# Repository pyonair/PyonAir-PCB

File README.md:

# PyonAir-PCB

This repository contains the files for the PyonAir air pollution monitor PCB.
These include:
-Eagle .brd and .sch files, which can be used to redesign the PCB.
-Zipped Gerber files, which are sent to PCB manufacturers.
-BOM for PCBA services

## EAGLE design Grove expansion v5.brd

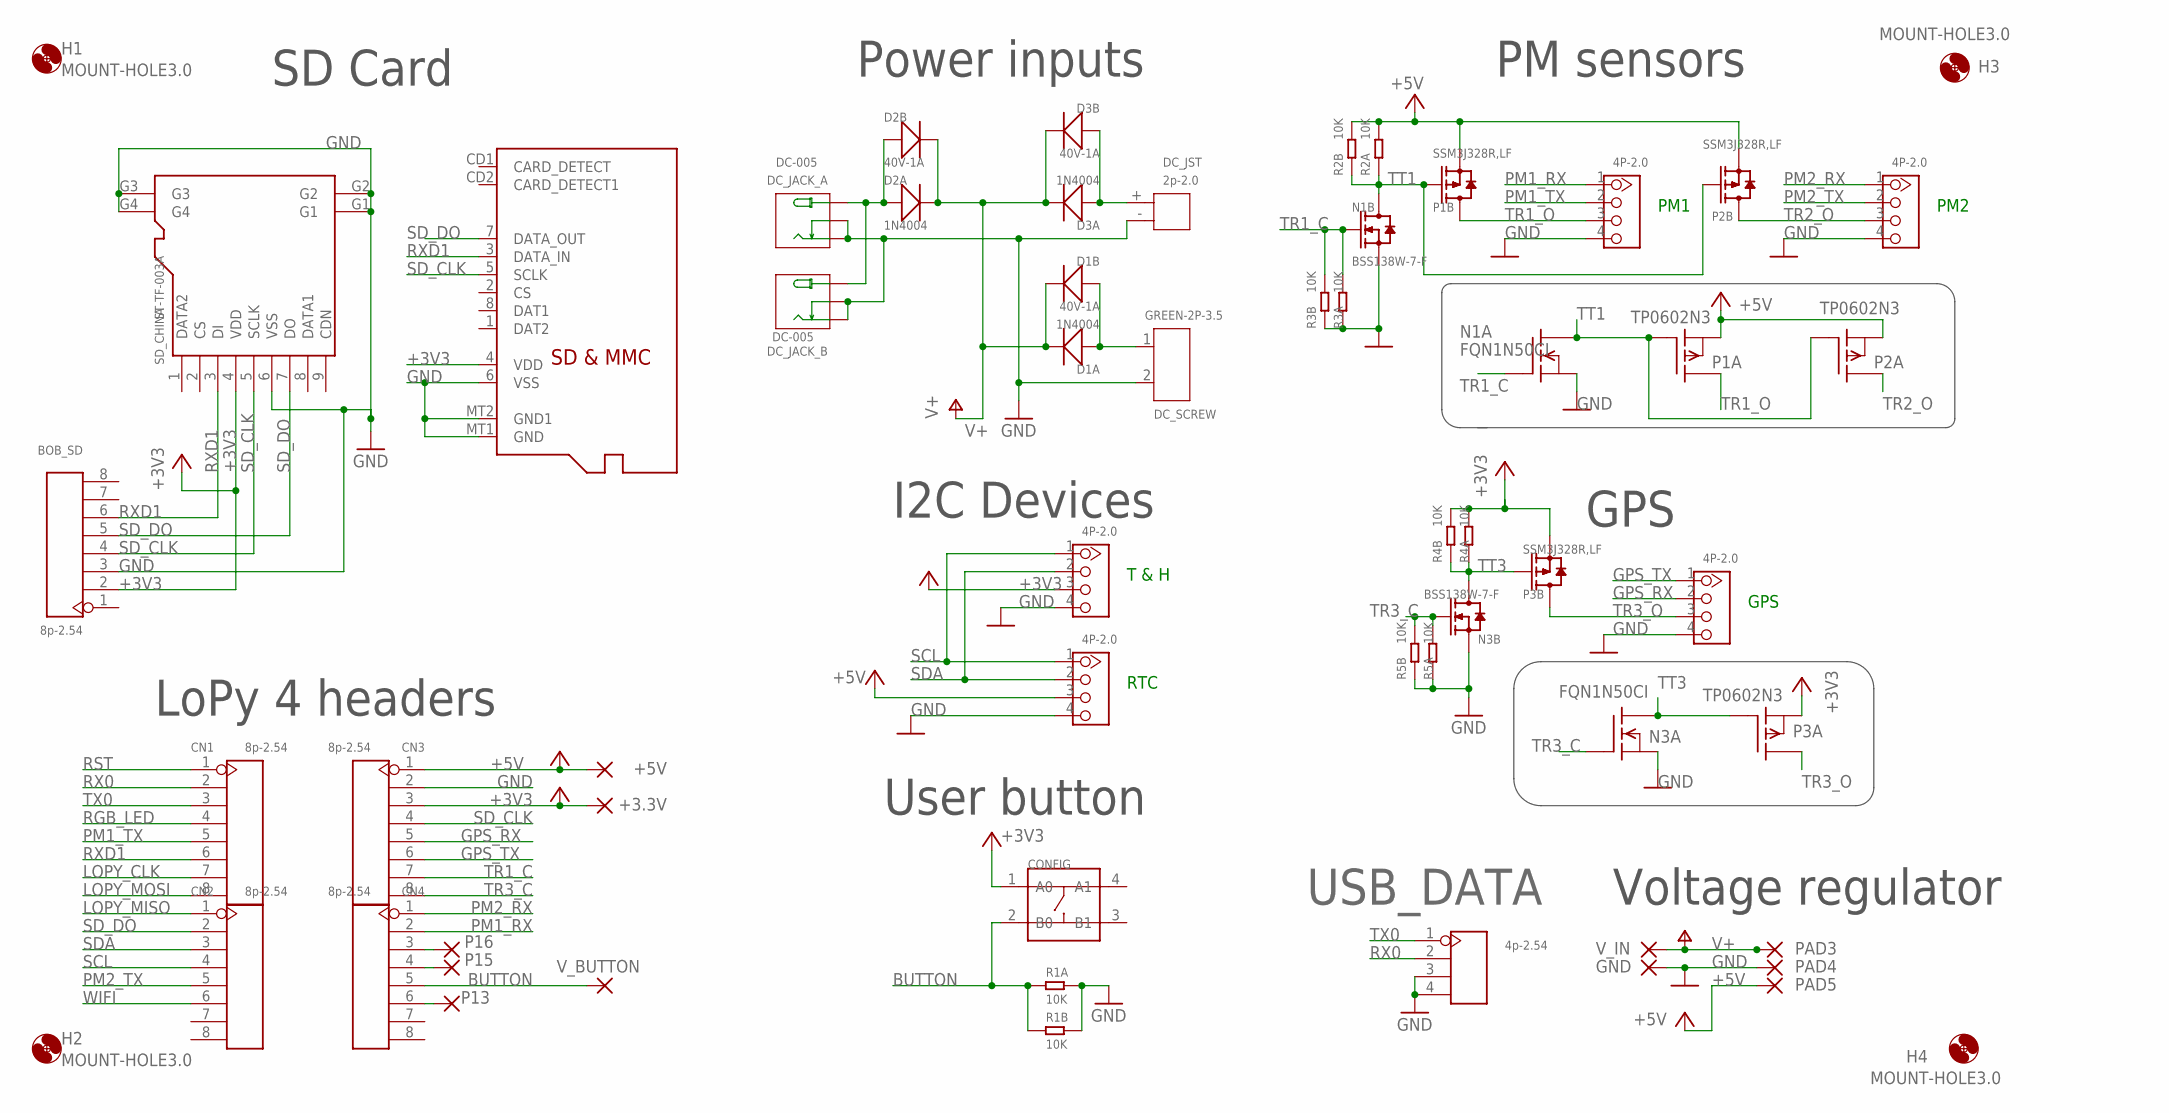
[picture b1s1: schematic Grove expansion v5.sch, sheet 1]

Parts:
+3.3V: 3.3V; 2,15/1,0
+5V: 5V; 2,15/1,0
BOB_SD: 8p-2.54; H8-2.54
CN1, CN2, CN3, CN4: 8p-2.54; H8-2.54
CONFIG: DIP-SWITCH-TACTILE-SPST-NO/TS-1109(4P-D6.0MM)'TS-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; SW4-6.0X6.0X5.0MM
D1A, D2A, D3A: 1N4004; DO-41
D1B, D2B, D3B: 40V-1A; DO-214AC
DC_JACK_A: DC-005; DCJ3P-14.2X11.0X9.0MM
DC_JACK_B: DC-005; DCJ3P-14.2X11.0X9.0MM
DC_JST: 2p-2.0; H2-2.0-6X4.5MM
DC_SCREW: GREEN-2P-3.5; H2-3.5-7.0X7.0MM
GND: 0V; 2,15/1,0
GPS-(DIG): 4P-2.0; HW4-2.0
H1, H2, H3, H4: MOUNT-HOLE3.0; 3,0
N1A, N3A: FQN1N50CI; TO92-INLINE
N1B, N3B: BSS138W-7-F; SOT-23
P1A, P2A, P3A: TP0602N3; TO-92
P1B, P2B, P3B: SSM3J328R,LF; SOT-23
P13, P15, P16: 2,15/1,0
PAD3: 12V; 1,6/0,8
PAD4: 0V; 1,6/0,8
PAD5: 5V; 1,6/0,8
PM1-(UART), PM2-(UART): 4P-2.0; HW4-2.0
R1A, R2A, R3A, R4A, R5A: 10K; PR-D2.3XL6.5MM
R1B, R2B, R3B, R4B, R5B: 10K; R0603
RTC-(I2C): 4P-2.0; HW4-2.0
SD_CHINA: ST-TF-003A; MICRO-SD9+4P-SMD-16.1X14.5X1.85MM
SD_UK: MICROSD
TH-(I2C): 4P-2.0; HW4-2.0
USB_DATA: 4p-2.54; H4-2.54
V_BUTTON: 3.3V; 2,15/1,0
V_IN: 12V; 2,15/1,0

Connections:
+3V3: +3.3V.1, BOB_SD.2, CN3.3, CONFIG.1 (A0), P3A.1 (S), P3B.2 (S), R4A.2, R4B.2, SD_CHINA.4 (VDD), SD_UK.4 (VDD), TH-(I2C).3
+5V: +5V.1, CN3.1, P1A.1 (S), P1B.2 (S), P2A.1 (S), P2B.2 (S), PAD5.1, R2A.2, R2B.2, RTC-(I2C).3
BUTTON: CN4.5, CONFIG.2 (B0), R1A.1, R1B.1, V_BUTTON.1
GND: BOB_SD.3, CN3.2, DC_JACK_A.-1 (-), DC_JACK_A.-2 (CDN), DC_JACK_B.-1 (-), DC_JACK_B.-2 (CDN), DC_JST.-, DC_SCREW.2, GND.1, GPS-(DIG).4, N1A.3 (S), N1B.2 (S), N3A.3 (S), N3B.2 (S), PAD4.1, PM1-(UART).4, PM2-(UART).4, R1A.2, R1B.2, R3A.1, R3B.1, R5A.1, R5B.1, RTC-(I2C).4, SD_CHINA.6 (VSS), SD_CHINA.G1, SD_CHINA.G2, SD_CHINA.G3, SD_CHINA.G4, SD_UK.6 (VSS), SD_UK.MT1 (GND), SD_UK.MT2 (GND1), TH-(I2C).4, USB_DATA.3, USB_DATA.4
GPS_RX: CN3.5, GPS-(DIG).2
GPS_TX: CN3.6, GPS-(DIG).1
JACK_V+: D2A.1 (+), D2B.1 (+), DC_JACK_A.+, DC_JACK_B.+
JST_V+: D3A.1 (+), D3B.1 (+), DC_JST.+
LOPY_CLK: CN1.7
LOPY_MISO: CN2.1
LOPY_MOSI: CN1.8
P13: CN4.6, P13.1
P15: CN4.4, P15.1
P16: CN4.3, P16.1
PM1_RX: CN4.2, PM1-(UART).1
PM1_TX: CN1.5, PM1-(UART).2
PM2_RX: CN4.1, PM2-(UART).1
PM2_TX: CN2.5, PM2-(UART).2
RGB_LED: CN1.4
RST: CN1.1
RX0: CN1.2, USB_DATA.2
RXD1: BOB_SD.6, CN1.6, SD_CHINA.3 (DI), SD_UK.3 (DATA_IN)
SCL: CN2.4, RTC-(I2C).1, TH-(I2C).1
SCREW_V+: D1A.1 (+), D1B.1 (+), DC_SCREW.1
SDA: CN2.3, RTC-(I2C).2, TH-(I2C).2
SD_CLK: BOB_SD.4, CN3.4, SD_CHINA.5 (SCLK), SD_UK.5 (SCLK)
SD_DO: BOB_SD.5, CN2.2, SD_CHINA.7 (DO), SD_UK.7 (DATA_OUT)
TR1_C: CN3.7, N1A.2 (G), N1B.1 (G), R3A.2, R3B.2
TR1_O: P1A.3 (D), P1B.3 (D), PM1-(UART).3
TR2_O: P2A.3 (D), P2B.3 (D), PM2-(UART).3
TR3_C: CN3.8, N3A.2 (G), N3B.1 (G), R5A.2, R5B.2
TR3_O: GPS-(DIG).3, P3A.3 (D), P3B.3 (D)
TT1: N1A.1 (D), N1B.3 (D), P1A.2 (G), P1B.1 (G), P2A.2 (G), P2B.1 (G), R2A.1, R2B.1
TT3: N3A.1 (D), N3B.3 (D), P3A.2 (G), P3B.1 (G), R4A.1, R4B.1
TX0: CN1.3, USB_DATA.1
V+: D1A.2 (-), D1B.2 (-), D2A.2 (-), D2B.2 (-), D3A.2 (-), D3B.2 (-), PAD3.1, V_IN.1
WIFI: CN2.6

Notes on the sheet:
PM1
PM2
T & H
GPS
RTC
Power inputs
User button
Voltage regulator
PM sensors
SD Card
LoPy 4 headers
I2C Devices

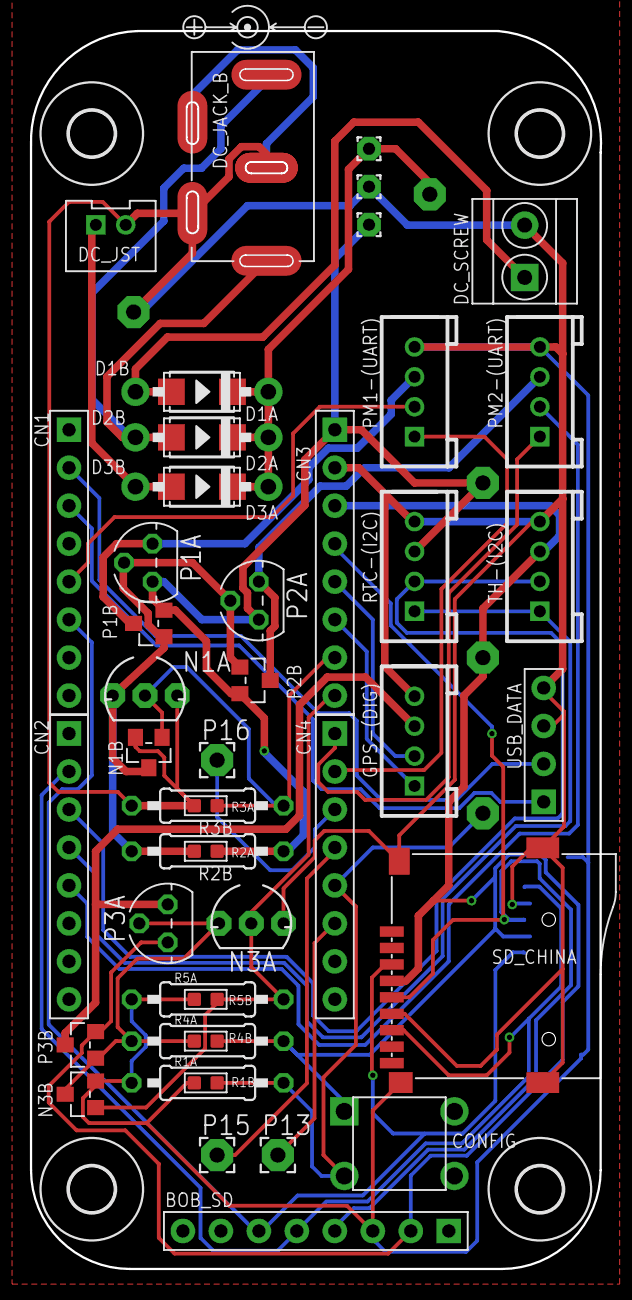
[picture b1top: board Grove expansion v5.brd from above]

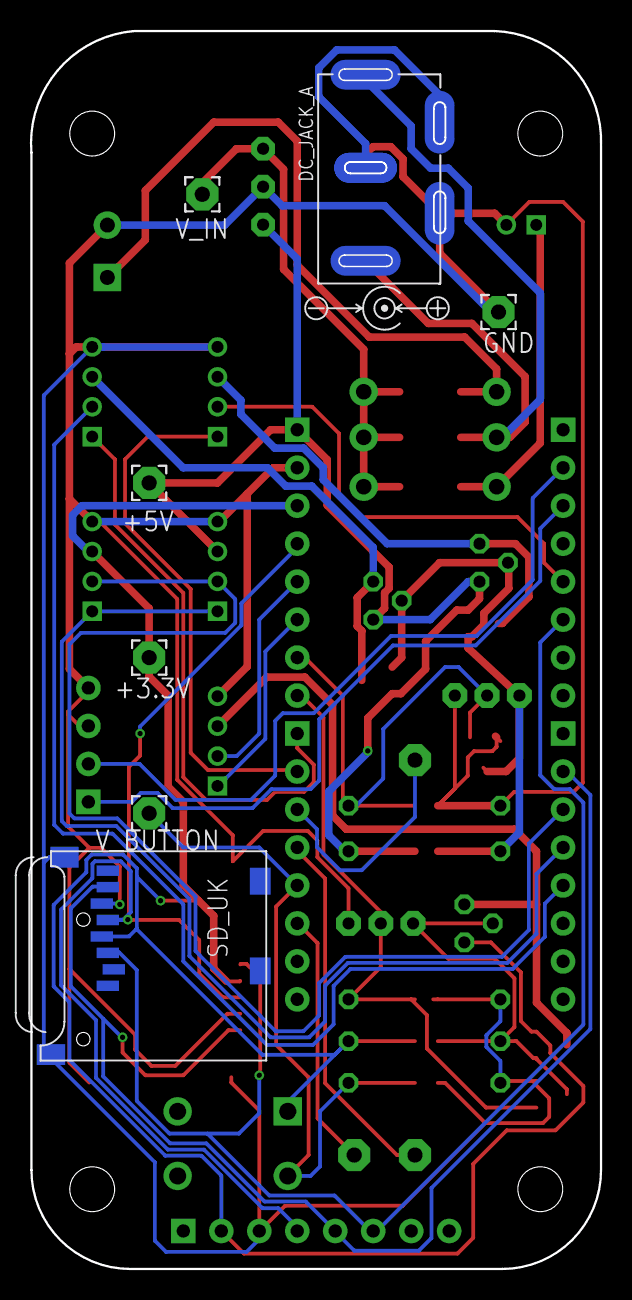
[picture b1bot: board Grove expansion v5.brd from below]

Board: 2 copper layers, 38.1 x 82.8 mm, 59 parts (7 on the bottom side), 31 nets.

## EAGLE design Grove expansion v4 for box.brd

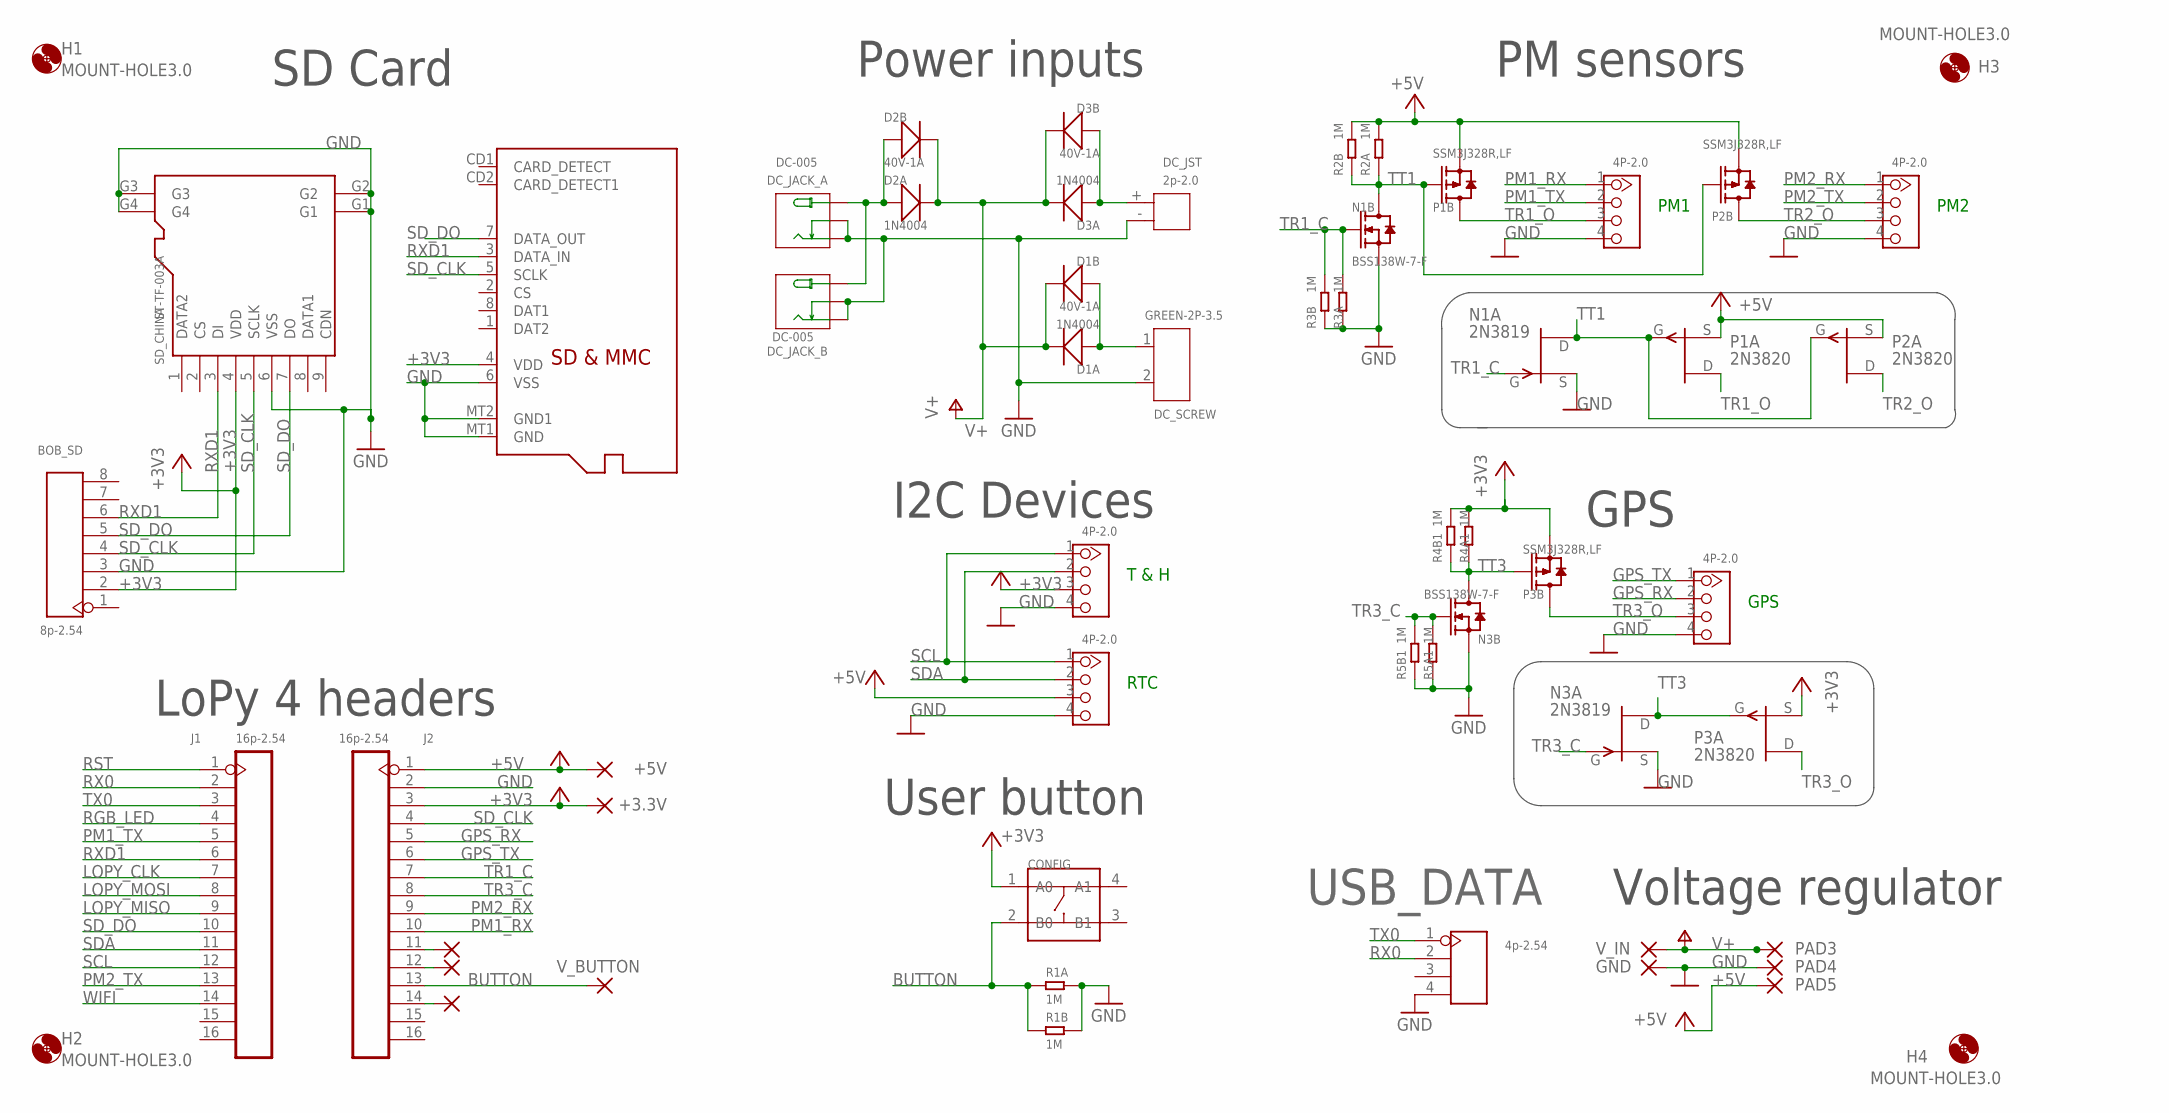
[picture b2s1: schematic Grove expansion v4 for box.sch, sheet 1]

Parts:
+3.3V, +5V: 2,15/1,0
BOB_SD: 8p-2.54; H8-2.54
CONFIG: DIP-SWITCH-TACTILE-SPST-NO/TS-1109(4P-D6.0MM)'TS-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; SW4-6.0X6.0X5.0MM
D1A, D2A, D3A: 1N4004; DO-41
D1B, D2B, D3B: 40V-1A; DO-214AC
DC_JACK_A: DC-005; DCJ3P-14.2X11.0X9.0MM
DC_JACK_B: DC-005; DCJ3P-14.2X11.0X9.0MM
DC_JST: 2p-2.0; H2-2.0-6X4.5MM
DC_SCREW: GREEN-2P-3.5; H2-3.5-7.0X7.0MM
GND: 2,15/1,0
GPS-(DIG): 4P-2.0; HW4-2.0
H1, H2, H3, H4: MOUNT-HOLE3.0; 3,0
J1, J2: 16p-2.54; H16-2.54
N1A, N3A: 2N3819; TO92
N1B, N3B: BSS138W-7-F; SOT-23
P1A, P2A, P3A: 2N3820; TO92
P1B, P2B, P3B: SSM3J328R,LF; SOT-23
P13, P15, P16: 2,15/1,0
PAD3, PAD4, PAD5: 1,6/0,8
PM1-(UART), PM2-(UART): 4P-2.0; HW4-2.0
R1A, R2A, R3A, R4A1, R5A1: 1M; PR-D2.3XL6.5MM
R1B, R2B, R3B, R4B1, R5B1: 1M; R0603
RTC-(I2C): 4P-2.0; HW4-2.0
SD_CHINA: ST-TF-003A; MICRO-SD9+4P-SMD-16.1X14.5X1.85MM
SD_UK: MICROSD
TH-(I2C): 4P-2.0; HW4-2.0
USB_DATA: 4p-2.54; H4-2.54
V_BUTTON: 2,15/1,0
V_IN: 2,15/1,0

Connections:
+3V3: +3.3V.1, BOB_SD.2, CONFIG.1 (A0), J2.3, P3A.1 (S), P3B.2 (S), R4A1.2, R4B1.2, SD_CHINA.4 (VDD), SD_UK.4 (VDD), TH-(I2C).3
+5V: +5V.1, J2.1, P1A.1 (S), P1B.2 (S), P2A.1 (S), P2B.2 (S), PAD5.1, R2A.2, R2B.2, RTC-(I2C).3
BUTTON: CONFIG.2 (B0), J2.13, R1A.1, R1B.1, V_BUTTON.1
GND: BOB_SD.3, DC_JACK_A.-1 (-), DC_JACK_A.-2 (CDN), DC_JACK_B.-1 (-), DC_JACK_B.-2 (CDN), DC_JST.-, DC_SCREW.2, GND.1, GPS-(DIG).4, J2.2, N1A.3 (S), N1B.2 (S), N3A.3 (S), N3B.2 (S), PAD4.1, PM1-(UART).4, PM2-(UART).4, R1A.2, R1B.2, R3A.1, R3B.1, R5A1.1, R5B1.1, RTC-(I2C).4, SD_CHINA.6 (VSS), SD_CHINA.G1, SD_CHINA.G2, SD_CHINA.G3, SD_CHINA.G4, SD_UK.6 (VSS), SD_UK.MT1 (GND), SD_UK.MT2 (GND1), TH-(I2C).4, USB_DATA.4
GPS_RX: GPS-(DIG).2, J2.5
GPS_TX: GPS-(DIG).1, J2.6
JACK_V+: D2A.1 (+), D2B.1 (+), DC_JACK_A.+, DC_JACK_B.+
JST_V+: D3A.1 (+), D3B.1 (+), DC_JST.+
LOPY_CLK: J1.7
LOPY_MISO: J1.9
LOPY_MOSI: J1.8
unnamed: J2.11, P16.1
unnamed: J2.12, P15.1
unnamed: J2.14, P13.1
PM1_RX: J2.10, PM1-(UART).1
PM1_TX: J1.5, PM1-(UART).2
PM2_RX: J2.9, PM2-(UART).1
PM2_TX: J1.13, PM2-(UART).2
RGB_LED: J1.4
RST: J1.1
RX0: J1.2, USB_DATA.2
RXD1: BOB_SD.6, J1.6, SD_CHINA.3 (DI), SD_UK.3 (DATA_IN)
SCL: J1.12, RTC-(I2C).1, TH-(I2C).1
SCREW_V+: D1A.1 (+), D1B.1 (+), DC_SCREW.1
SDA: J1.11, RTC-(I2C).2, TH-(I2C).2
SD_CLK: BOB_SD.4, J2.4, SD_CHINA.5 (SCLK), SD_UK.5 (SCLK)
SD_DO: BOB_SD.5, J1.10, SD_CHINA.7 (DO), SD_UK.7 (DATA_OUT)
TR1_C: J2.7, N1A.2 (G), N1B.1 (G), R3A.2, R3B.2
TR1_O: P1A.3 (D), P1B.3 (D), PM1-(UART).3
TR2_O: P2A.3 (D), P2B.3 (D), PM2-(UART).3
TR3_C: J2.8, N3A.2 (G), N3B.1 (G), R5A1.2, R5B1.2
TR3_O: GPS-(DIG).3, P3A.3 (D), P3B.3 (D)
TT1: N1A.1 (D), N1B.3 (D), P1A.2 (G), P1B.1 (G), P2A.2 (G), P2B.1 (G), R2A.1, R2B.1
TT3: N3A.1 (D), N3B.3 (D), P3A.2 (G), P3B.1 (G), R4A1.1, R4B1.1
TX0: J1.3, USB_DATA.1
V+: D1A.2 (-), D1B.2 (-), D2A.2 (-), D2B.2 (-), D3A.2 (-), D3B.2 (-), PAD3.1, V_IN.1
WIFI: J1.14

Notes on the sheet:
PM1
PM2
T & H
GPS
RTC
Power inputs
User button
Voltage regulator
PM sensors
SD Card
LoPy 4 headers
I2C Devices

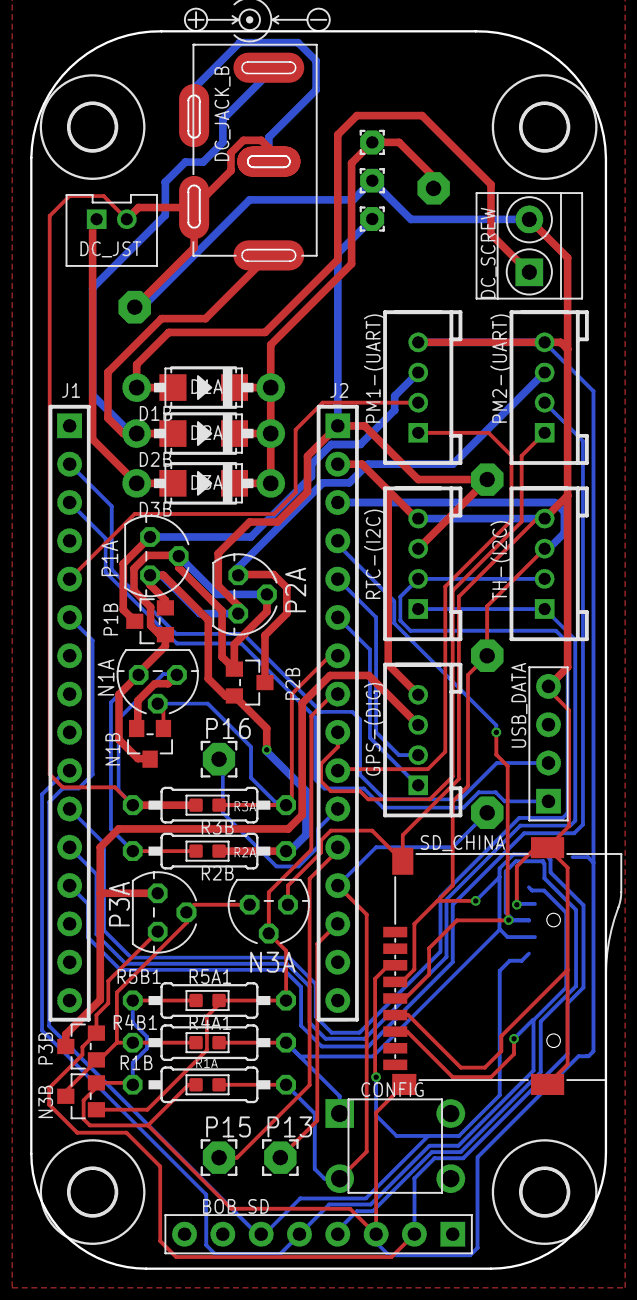
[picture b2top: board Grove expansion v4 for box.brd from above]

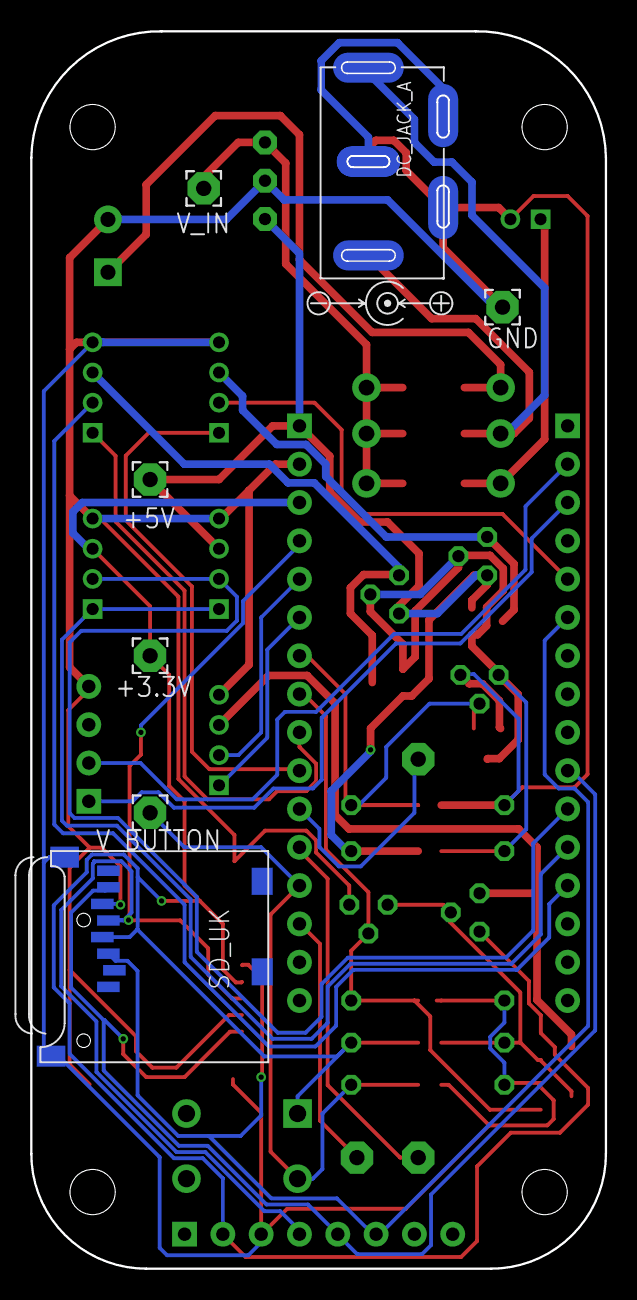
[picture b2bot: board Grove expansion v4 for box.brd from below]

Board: 2 copper layers, 38.1 x 82.0 mm, 57 parts (7 on the bottom side), 31 nets.

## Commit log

2019-08-21 Upload PCB V4 Eagle files
2019-09-06 Add final Gerber files
2019-09-06 Add V5 Eagle files
2019-09-12 Fixed header issue
2019-09-16 PDF files showing V5 board and schematic
2019-09-16 Add license

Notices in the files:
Grove expansion v4 for box.brd:
CC-BY-SA
